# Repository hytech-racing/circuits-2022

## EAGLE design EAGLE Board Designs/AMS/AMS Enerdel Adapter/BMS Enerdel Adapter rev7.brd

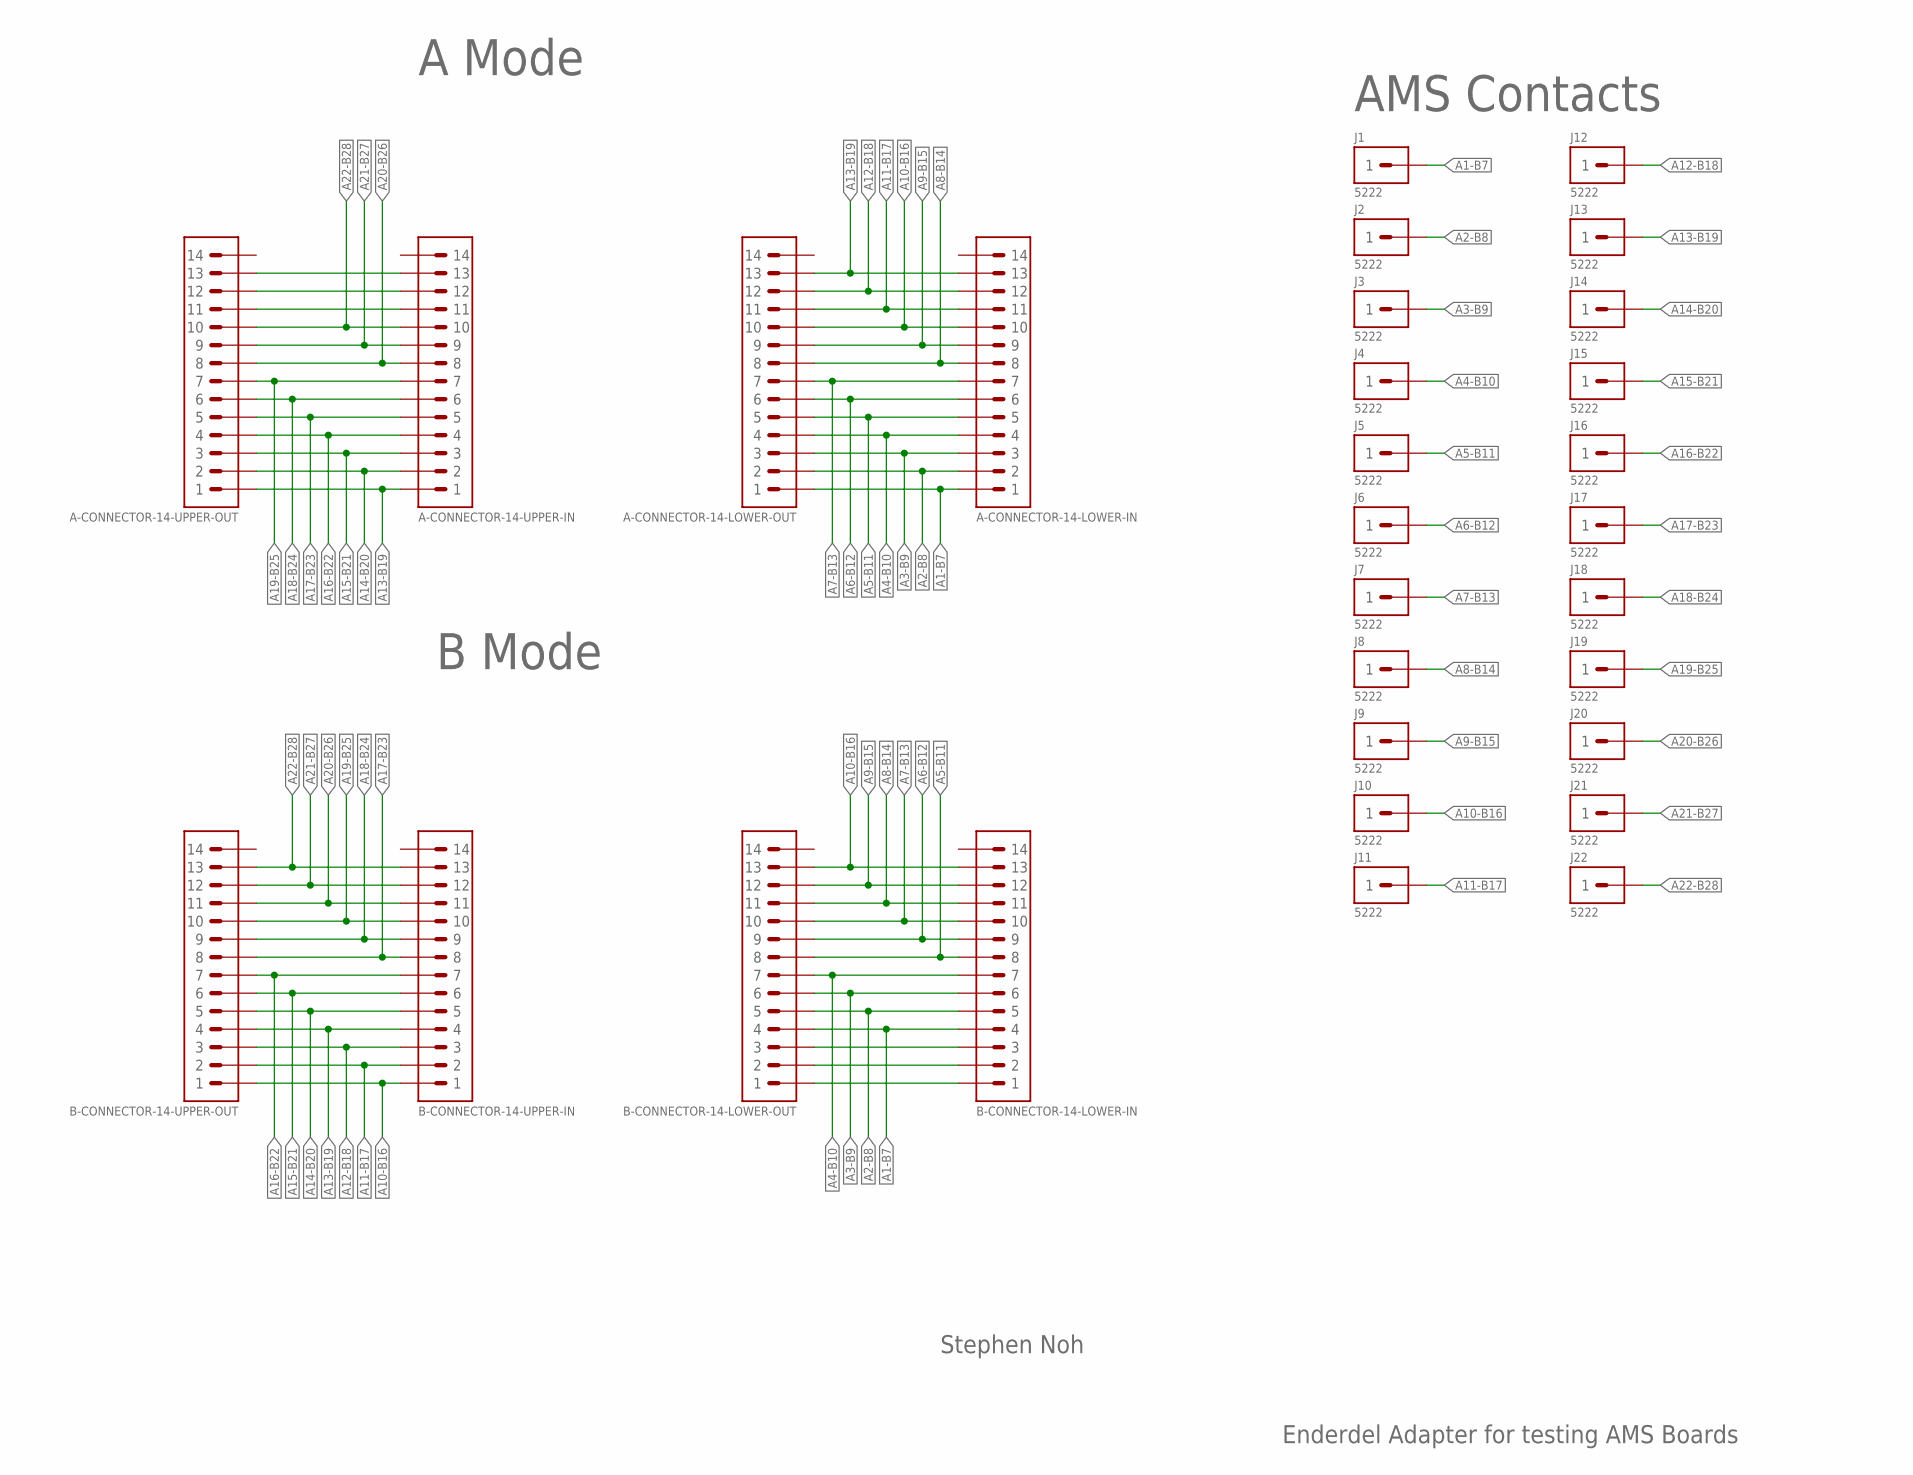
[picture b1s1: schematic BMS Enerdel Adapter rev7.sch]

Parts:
A-CONNECTOR-14-LOWER-IN, A-CONNECTOR-14-LOWER-OUT: CONNECTOR-14_MINIFIT_; MOLEX_MINIFIT_PTH_14
A-CONNECTOR-14-UPPER-IN, A-CONNECTOR-14-UPPER-OUT: CONNECTOR-14_NANOFIT_; MOLEX_NANOFIT_PTH_14
B-CONNECTOR-14-LOWER-IN, B-CONNECTOR-14-LOWER-OUT: CONNECTOR-14_MINIFIT_; MOLEX_MINIFIT_PTH_14
B-CONNECTOR-14-UPPER-IN, B-CONNECTOR-14-UPPER-OUT: CONNECTOR-14_NANOFIT_; MOLEX_NANOFIT_PTH_14
J1, J2, J3, J4, J5, J6, J7, J8, J9, J10, J11, J12, J13, J14, J15, J16, J17, J18, J19, J20, J21, J22: CONNECTOR-1_5222_; 5222

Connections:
A1-B7: A-CONNECTOR-14-LOWER-IN.1, A-CONNECTOR-14-LOWER-OUT.1, B-CONNECTOR-14-LOWER-IN.4, B-CONNECTOR-14-LOWER-OUT.4, J1.1
A2-B8: A-CONNECTOR-14-LOWER-IN.2, A-CONNECTOR-14-LOWER-OUT.2, B-CONNECTOR-14-LOWER-IN.5, B-CONNECTOR-14-LOWER-OUT.5, J2.1
A3-B9: A-CONNECTOR-14-LOWER-IN.3, A-CONNECTOR-14-LOWER-OUT.3, B-CONNECTOR-14-LOWER-IN.6, B-CONNECTOR-14-LOWER-OUT.6, J3.1
A4-B10: A-CONNECTOR-14-LOWER-IN.4, A-CONNECTOR-14-LOWER-OUT.4, B-CONNECTOR-14-LOWER-IN.7, B-CONNECTOR-14-LOWER-OUT.7, J4.1
A5-B11: A-CONNECTOR-14-LOWER-IN.5, A-CONNECTOR-14-LOWER-OUT.5, B-CONNECTOR-14-LOWER-IN.8, B-CONNECTOR-14-LOWER-OUT.8, J5.1
A6-B12: A-CONNECTOR-14-LOWER-IN.6, A-CONNECTOR-14-LOWER-OUT.6, B-CONNECTOR-14-LOWER-IN.9, B-CONNECTOR-14-LOWER-OUT.9, J6.1
A7-B13: A-CONNECTOR-14-LOWER-IN.7, A-CONNECTOR-14-LOWER-OUT.7, B-CONNECTOR-14-LOWER-IN.10, B-CONNECTOR-14-LOWER-OUT.10, J7.1
A8-B14: A-CONNECTOR-14-LOWER-IN.8, A-CONNECTOR-14-LOWER-OUT.8, B-CONNECTOR-14-LOWER-IN.11, B-CONNECTOR-14-LOWER-OUT.11, J8.1
A9-B15: A-CONNECTOR-14-LOWER-IN.9, A-CONNECTOR-14-LOWER-OUT.9, B-CONNECTOR-14-LOWER-IN.12, B-CONNECTOR-14-LOWER-OUT.12, J9.1
A10-B16: A-CONNECTOR-14-LOWER-IN.10, A-CONNECTOR-14-LOWER-OUT.10, B-CONNECTOR-14-LOWER-IN.13, B-CONNECTOR-14-LOWER-OUT.13, B-CONNECTOR-14-UPPER-IN.1, B-CONNECTOR-14-UPPER-OUT.1, J10.1
A11-B17: A-CONNECTOR-14-LOWER-IN.11, A-CONNECTOR-14-LOWER-OUT.11, B-CONNECTOR-14-UPPER-IN.2, B-CONNECTOR-14-UPPER-OUT.2, J11.1
A12-B18: A-CONNECTOR-14-LOWER-IN.12, A-CONNECTOR-14-LOWER-OUT.12, B-CONNECTOR-14-UPPER-IN.3, B-CONNECTOR-14-UPPER-OUT.3, J12.1
A13-B19: A-CONNECTOR-14-LOWER-IN.13, A-CONNECTOR-14-LOWER-OUT.13, A-CONNECTOR-14-UPPER-IN.1, A-CONNECTOR-14-UPPER-OUT.1, B-CONNECTOR-14-UPPER-IN.4, B-CONNECTOR-14-UPPER-OUT.4, J13.1
A14-B20: A-CONNECTOR-14-UPPER-IN.2, A-CONNECTOR-14-UPPER-OUT.2, B-CONNECTOR-14-UPPER-IN.5, B-CONNECTOR-14-UPPER-OUT.5, J14.1
A15-B21: A-CONNECTOR-14-UPPER-IN.3, A-CONNECTOR-14-UPPER-OUT.3, B-CONNECTOR-14-UPPER-IN.6, B-CONNECTOR-14-UPPER-OUT.6, J15.1
A16-B22: A-CONNECTOR-14-UPPER-IN.4, A-CONNECTOR-14-UPPER-OUT.4, B-CONNECTOR-14-UPPER-IN.7, B-CONNECTOR-14-UPPER-OUT.7, J16.1
A17-B23: A-CONNECTOR-14-UPPER-IN.5, A-CONNECTOR-14-UPPER-OUT.5, B-CONNECTOR-14-UPPER-IN.8, B-CONNECTOR-14-UPPER-OUT.8, J17.1
A18-B24: A-CONNECTOR-14-UPPER-IN.6, A-CONNECTOR-14-UPPER-OUT.6, B-CONNECTOR-14-UPPER-IN.9, B-CONNECTOR-14-UPPER-OUT.9, J18.1
A19-B25: A-CONNECTOR-14-UPPER-IN.7, A-CONNECTOR-14-UPPER-OUT.7, B-CONNECTOR-14-UPPER-IN.10, B-CONNECTOR-14-UPPER-OUT.10, J19.1
A20-B26: A-CONNECTOR-14-UPPER-IN.8, A-CONNECTOR-14-UPPER-OUT.8, B-CONNECTOR-14-UPPER-IN.11, B-CONNECTOR-14-UPPER-OUT.11, J20.1
A21-B27: A-CONNECTOR-14-UPPER-IN.9, A-CONNECTOR-14-UPPER-OUT.9, B-CONNECTOR-14-UPPER-IN.12, B-CONNECTOR-14-UPPER-OUT.12, J21.1
A22-B28: A-CONNECTOR-14-UPPER-IN.10, A-CONNECTOR-14-UPPER-OUT.10, B-CONNECTOR-14-UPPER-IN.13, B-CONNECTOR-14-UPPER-OUT.13, J22.1
B-PASS1: B-CONNECTOR-14-LOWER-IN.3, B-CONNECTOR-14-LOWER-OUT.3
B-PASS2: B-CONNECTOR-14-LOWER-IN.2, B-CONNECTOR-14-LOWER-OUT.2
B-PASS3: B-CONNECTOR-14-LOWER-IN.1, B-CONNECTOR-14-LOWER-OUT.1
unnamed: A-CONNECTOR-14-UPPER-IN.11, A-CONNECTOR-14-UPPER-OUT.11
unnamed: A-CONNECTOR-14-UPPER-IN.12, A-CONNECTOR-14-UPPER-OUT.12
unnamed: A-CONNECTOR-14-UPPER-IN.13, A-CONNECTOR-14-UPPER-OUT.13

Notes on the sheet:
Stephen Noh
AMS Contacts
A Mode
Enderdel Adapter for testing AMS Boards
B Mode

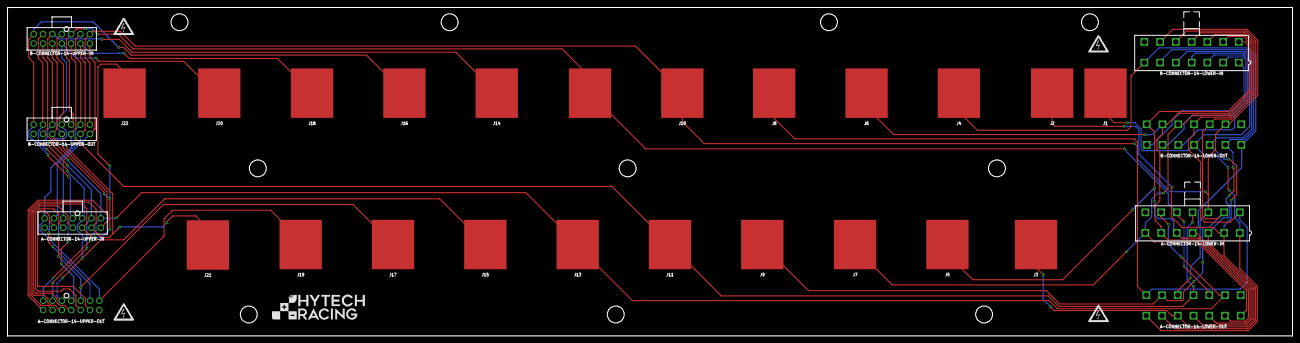
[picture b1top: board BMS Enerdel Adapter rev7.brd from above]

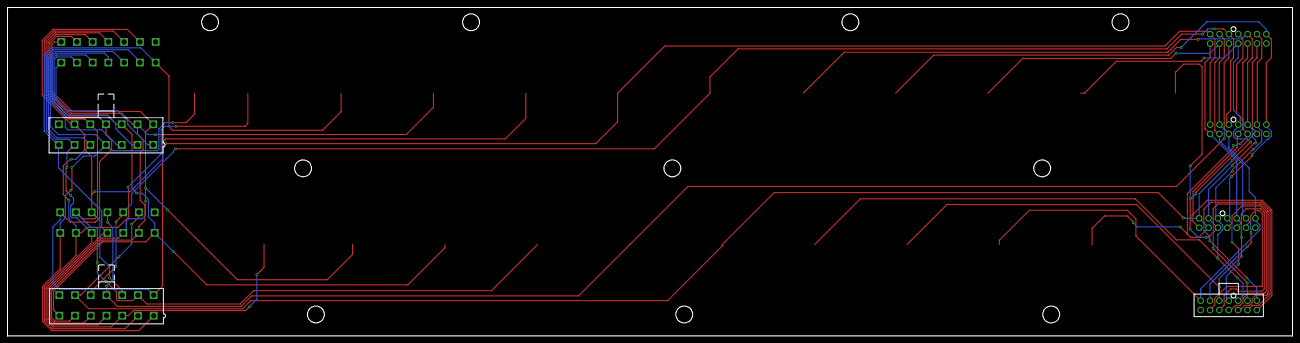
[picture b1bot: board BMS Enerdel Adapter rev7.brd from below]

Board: 2 copper layers, 342.9 x 87.6 mm, 35 parts (3 on the bottom side), 28 nets.

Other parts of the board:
U$1, U$3, U$4, U$5: HV_0.50"
U$2: LOGO_HYTECH_1.0"

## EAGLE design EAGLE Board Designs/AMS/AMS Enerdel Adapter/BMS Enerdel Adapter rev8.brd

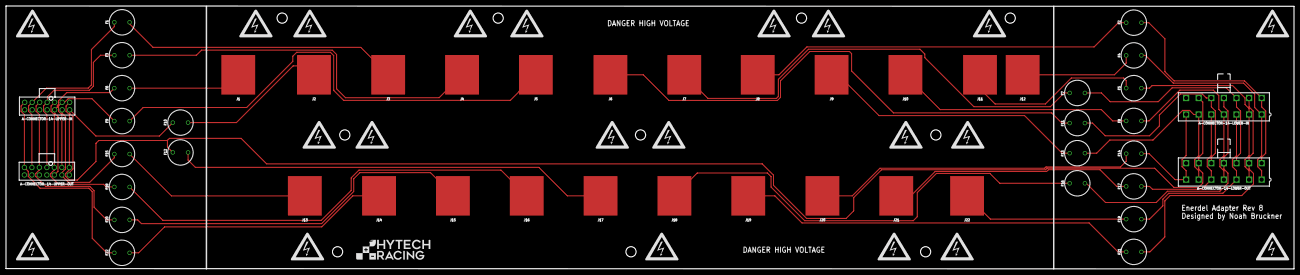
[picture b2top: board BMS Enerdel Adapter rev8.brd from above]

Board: 2 copper layers, 429.8 x 87.7 mm, 80 parts (0 on the bottom side), 44 nets.

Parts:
A-CONNECTOR-14-LOWER-IN, A-CONNECTOR-14-LOWER-OUT: CONNECTOR-14_MINIFIT_; MOLEX_MINIFIT_PTH_14
A-CONNECTOR-14-UPPER-IN, A-CONNECTOR-14-UPPER-OUT: CONNECTOR-14_NANOFIT_; MOLEX_NANOFIT_PTH_14
F1, F2, F3, F4, F5, F6, F7, F8, F9, F10, F11, F12, F13, F14, F15, F16, F17, F18, F19, F20, F21, F22: FUSE_MST_250_.8; MST_250
J1, J2, J3, J4, J5, J6, J7, J8, J9, J10, J11, J12, J13, J14, J15, J16, J17, J18, J19, J20, J21, J22: CONNECTOR-1_5222_; 5222
U$1, U$2, U$3, U$4, U$20, U$21, U$22, U$29, U$30, U$31: MOUNTING_M3
U$5, U$6, U$7, U$8, U$9, U$10, U$11, U$12, U$13, U$14, U$15, U$16, U$17, U$18, U$19, U$23, U$24, U$25, U$26, U$27, U$28: HV_LARGE
U$32: LOGO_HYTECH_1.0"

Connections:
A1-B7: A-CONNECTOR-14-LOWER-IN.1, A-CONNECTOR-14-LOWER-OUT.1, F4.2
A2-B8: A-CONNECTOR-14-LOWER-IN.2, A-CONNECTOR-14-LOWER-OUT.2, F5.2
A3-B9: A-CONNECTOR-14-LOWER-IN.3, A-CONNECTOR-14-LOWER-OUT.3, F19.2
A4-B10: A-CONNECTOR-14-LOWER-IN.4, A-CONNECTOR-14-LOWER-OUT.4, F8.2
A5-B11: A-CONNECTOR-14-LOWER-IN.5, A-CONNECTOR-14-LOWER-OUT.5, F17.2
A6-B12: A-CONNECTOR-14-LOWER-IN.6, A-CONNECTOR-14-LOWER-OUT.6, F13.2
A7-B13: A-CONNECTOR-14-LOWER-IN.7, A-CONNECTOR-14-LOWER-OUT.7, F14.2
A8-B14: A-CONNECTOR-14-LOWER-IN.8, A-CONNECTOR-14-LOWER-OUT.8, F2.2
A9-B15: A-CONNECTOR-14-LOWER-IN.9, A-CONNECTOR-14-LOWER-OUT.9, F21.2
A10-B16: A-CONNECTOR-14-LOWER-IN.10, A-CONNECTOR-14-LOWER-OUT.10, F7.2
A11-B17: A-CONNECTOR-14-LOWER-IN.11, A-CONNECTOR-14-LOWER-OUT.11, F16.2
A12-B18: A-CONNECTOR-14-LOWER-IN.12, A-CONNECTOR-14-LOWER-OUT.12, F11.2
A13-B19: A-CONNECTOR-14-LOWER-IN.13, A-CONNECTOR-14-LOWER-OUT.13, A-CONNECTOR-14-UPPER-IN.1, A-CONNECTOR-14-UPPER-OUT.1, F12.2
A14-B20: A-CONNECTOR-14-UPPER-IN.2, A-CONNECTOR-14-UPPER-OUT.2, F9.2
A15-B21: A-CONNECTOR-14-UPPER-IN.3, A-CONNECTOR-14-UPPER-OUT.3, F18.2
A16-B22: A-CONNECTOR-14-UPPER-IN.4, A-CONNECTOR-14-UPPER-OUT.4, F3.2
A17-B23: A-CONNECTOR-14-UPPER-IN.5, A-CONNECTOR-14-UPPER-OUT.5, F20.2
A18-B24: A-CONNECTOR-14-UPPER-IN.6, A-CONNECTOR-14-UPPER-OUT.6, F1.2
A19-B25: A-CONNECTOR-14-UPPER-IN.7, A-CONNECTOR-14-UPPER-OUT.7, F22.2
A20-B26: A-CONNECTOR-14-UPPER-IN.8, A-CONNECTOR-14-UPPER-OUT.8, F10.2
A21-B27: A-CONNECTOR-14-UPPER-IN.9, A-CONNECTOR-14-UPPER-OUT.9, F15.2
A22-B28: A-CONNECTOR-14-UPPER-IN.10, A-CONNECTOR-14-UPPER-OUT.10, F6.2
unnamed: F4.1, J12.1
unnamed: F5.1, J11.1
unnamed: F19.1, J22.1
unnamed: F8.1, J10.1
unnamed: F17.1, J21.1
unnamed: F13.1, J9.1
unnamed: F14.1, J20.1
unnamed: F2.1, J8.1
unnamed: F21.1, J19.1
unnamed: F7.1, J7.1
unnamed: F16.1, J18.1
unnamed: F6.1, J1.1
unnamed: F15.1, J13.1
unnamed: F10.1, J2.1
unnamed: F22.1, J14.1
unnamed: F1.1, J3.1
unnamed: F20.1, J15.1
unnamed: F3.1, J4.1
unnamed: F18.1, J16.1
unnamed: F9.1, J5.1
unnamed: F11.1, J6.1
unnamed: F12.1, J17.1

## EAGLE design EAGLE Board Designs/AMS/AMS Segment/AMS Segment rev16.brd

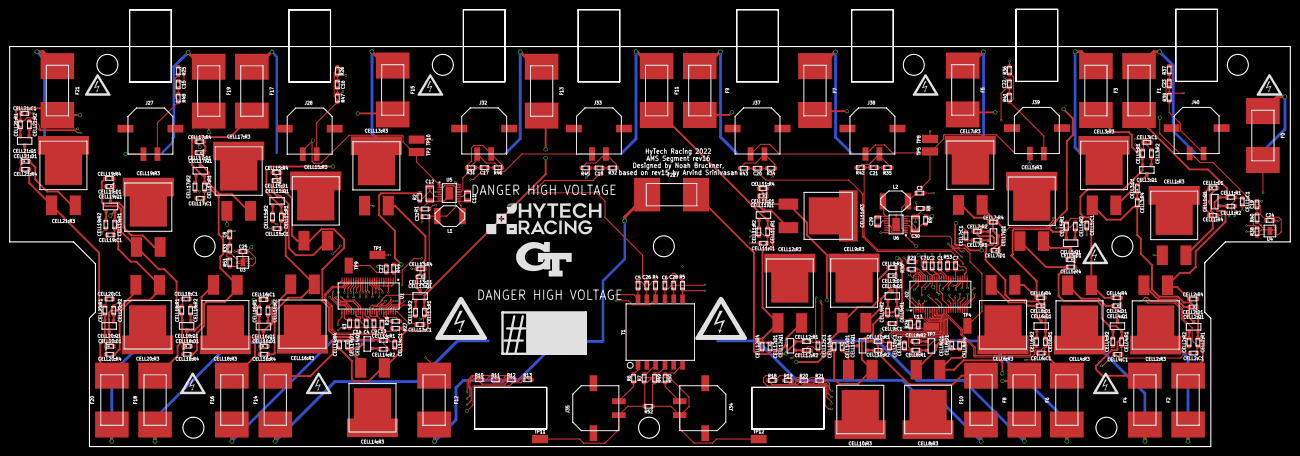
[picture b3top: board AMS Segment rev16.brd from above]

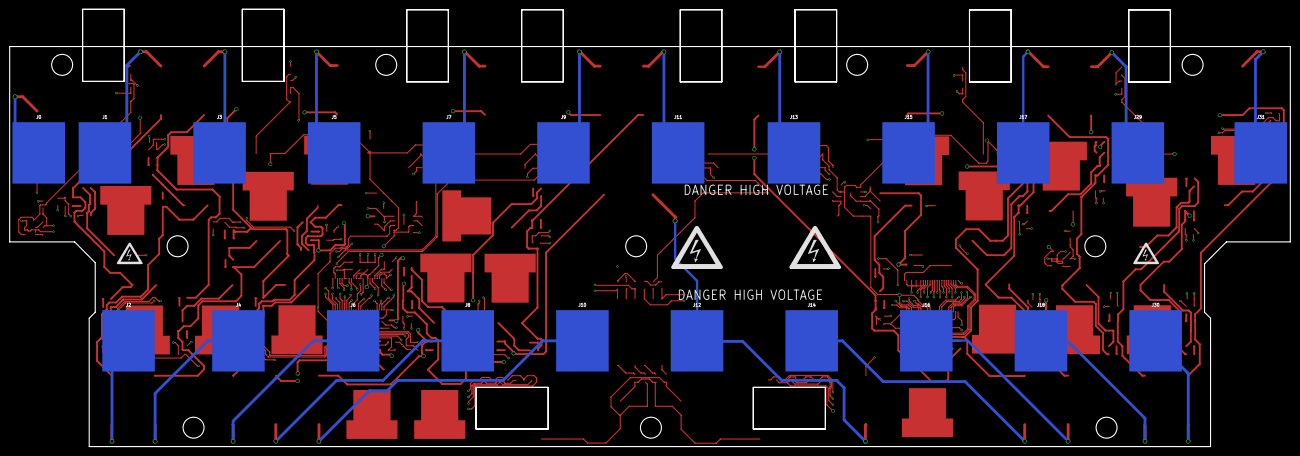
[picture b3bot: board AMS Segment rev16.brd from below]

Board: 4 copper layers, 275.2 x 94.0 mm, 329 parts (26 on the bottom side), 214 nets.

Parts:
C1, C2, C4, C9, C31, C32: CAPACITOR_0603_10V_1UF; 0603-CAP
C3, C10: CAPACITOR_0603_10V_22UF; 0603-CAP
C5, C6: CAPACITOR_0603_10V_15PF; 0603-CAP
C7, C14, C15, C16, C17, C18, C20, C21, C22, C23: CAPACITOR_0603_100V_10NF; 0603-CAP
C8, C19: CAPACITOR_0603_10V_3.3NF; 0603-CAP
C11, C29: CAPACITOR_0805_100V_0.22UF; 0805-CAP
C12, C30: CAPACITOR_1206_100V_2.2UF; 1206-CAP
C13, C27: CAPACITOR_0603_100V_0.1UF; 0603-CAP
C24, C25: CAPACITOR_0603_10V_0.1UF; 0603-CAP
C26, C28: CAPACITOR_0603_10V_10NF; 0603-CAP
CELL1:C1, CELL2:C1, CELL3:C1, CELL4:C1, CELL5:C1, CELL6:C1, CELL7:C1, CELL8:C1, CELL9:C1, CELL10:C1, CELL11:C1, CELL12:C1, CELL13:C1, CELL14:C1, CELL15:C1, CELL16:C1, CELL17:C1, CELL18:C1, CELL19:C1, CELL20:C1, CELL21:C1: CAPACITOR_0603_100V_10NF; 0603-CAP
CELL1:D1, CELL2:D1, CELL3:D1, CELL4:D1, CELL5:D1, CELL6:D1, CELL7:D1, CELL8:D1, CELL9:D1, CELL10:D1, CELL11:D1, CELL12:D1, CELL13:D1, CELL14:D1, CELL15:D1, CELL16:D1, CELL17:D1, CELL18:D1, CELL19:D1, CELL20:D1, CELL21:D1: LED_0603_RED; 0603-LED
CELL1:Q1, CELL2:Q1, CELL3:Q1, CELL4:Q1, CELL5:Q1, CELL6:Q1, CELL7:Q1, CELL8:Q1, CELL9:Q1, CELL10:Q1, CELL11:Q1, CELL12:Q1, CELL13:Q1, CELL14:Q1, CELL15:Q1, CELL16:Q1, CELL17:Q1, CELL18:Q1, CELL19:Q1, CELL20:Q1, CELL21:Q1: TRANSISTOR_P_MOS_SOT23_SI2369DS-T1-GE3; SOT-23
CELL1:R1, CELL2:R1, CELL3:R1, CELL4:R1, CELL5:R1, CELL6:R1, CELL7:R1, CELL8:R1, CELL9:R1, CELL10:R1, CELL11:R1, CELL12:R1, CELL13:R1, CELL14:R1, CELL15:R1, CELL16:R1, CELL17:R1, CELL18:R1, CELL19:R1, CELL20:R1, CELL21:R1: RESISTOR_0603_100; 0603-RES
CELL1:R2, CELL1:R4, CELL2:R2, CELL2:R4, CELL3:R2, CELL3:R4, CELL4:R2, CELL4:R4, CELL5:R2, CELL5:R4, CELL6:R2, CELL6:R4, CELL7:R2, CELL7:R4, CELL8:R2, CELL8:R4, CELL9:R2, CELL9:R4, CELL10:R2, CELL10:R4, CELL11:R2, CELL11:R4, CELL12:R2, CELL12:R4, CELL13:R2, CELL13:R4, CELL14:R2, CELL14:R4, CELL15:R2, CELL15:R4, CELL16:R2, CELL16:R4, CELL17:R2, CELL17:R4, CELL18:R2, CELL18:R4, CELL19:R2, CELL19:R4, CELL20:R2, CELL20:R4, CELL21:R2, CELL21:R4: RESISTOR_0603_1K; 0603-RES
CELL1:R3, CELL2:R3, CELL3:R3, CELL4:R3, CELL5:R3, CELL6:R3, CELL7:R3, CELL8:R3, CELL9:R3, CELL10:R3, CELL11:R3, CELL12:R3, CELL13:R3, CELL14:R3, CELL15:R3, CELL16:R3, CELL17:R3, CELL18:R3, CELL19:R3, CELL20:R3, CELL21:R3: RESISTOR_PWR263_7.5; PWR263
F0, F1, F2, F3, F4, F5, F6, F7, F8, F9, F10, F11, F12, F13, F14, F15, F16, F17, F18, F19, F20, F21, F22: FUSE_0885_1.6; 0885
J0, J1, J2, J3, J4, J5, J6, J7, J8, J9, J10, J11, J12, J13, J14, J15, J16, J17, J18, J29, J30, J31: CONNECTOR-1_5222_; 5222
J27, J28, J32, J33, J34, J35, J37, J38, J39, J40: CONNECTOR-2_MICROFIT_SMD_RIGHTANGLE_02_SINGLE_BLA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; MOLEX_MICROFIT_SMD_RIGHTANGLE_02_SINGLE
L1, L2: INDUCTOR_74451133_33UH; 74451133
R1, R8: RESISTOR_0603_374K; 0603-RES
R2, R9: RESISTOR_0603_470; 0603-RES
R3, R24, R33, R38, R39, R41, R42, R43, R44, R45, R46, R47, R48, R53: RESISTOR_0603_100; 0603-RES
R4, R5: RESISTOR_0603_402; 0603-RES
R6, R7, R49, R50: RESISTOR_0603_22; 0603-RES
R10, R11, R12, R13, R18, R19, R20, R21, R40, R51, R52: RESISTOR_0603_DNP; 0603-RES
R25, R26, R31, R32, R34, R35, R36, R37: RESISTOR_0603_2.74K; 0603-RES
R27, R28, R29, R30: RESISTOR_0603_1K; 0603-RES
T1: TRANSFORMER_HM2112ZNLT; HM2112ZNLT
TP1, TP2, TP4, TP5, TP7, TP8, TP9, TP10, TP11, TP12: TEST_POINT; MICRO_MINIATURE
U1, U2: LTC6811-2; SSOP-48
U3, U4: SHT31-ARP-B; DFN-8
U5, U6: LT3990-5; MSOP-16(MSE)
U$1, U$4, U$5, U$6, U$11, U$12, U$13, U$14, U$15, U$16: MOUNTING_M4
U$2: LOGO_HYTECH_1.0"
U$3: LOGO_GT_0.50"
U$7: NUMBER
U$8, U$9, U$10, U$17, U$18, U$19, U$20, U$22, U$28, U$29: HV_0.50"
U$21, U$25: DANGER_HIGH_VOLTAGE
U$23, U$24, U$26, U$27: HV_1.00"

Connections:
C0L: C7.1, R53.2, U2.26
C0U: C14.1, R3.2, U1.26
C1L: CELL1:C1.1, CELL1:R1.2, U2.24
C1U: CELL13:C1.1, CELL13:R1.2, U1.24
C2L: CELL2:C1.1, CELL2:R1.2, U2.22
C2U: CELL14:C1.1, CELL14:R1.2, U1.22
C3L: CELL3:C1.1, CELL3:R1.2, U2.20
C3U: CELL15:C1.1, CELL15:R1.2, U1.20
C4L: CELL4:C1.1, CELL4:R1.2, U2.18
C4U: CELL16:C1.1, CELL16:R1.2, U1.18
C5L: CELL5:C1.1, CELL5:R1.2, U2.16
C5U: CELL17:C1.1, CELL17:R1.2, U1.16
C6L: CELL6:C1.1, CELL6:R1.2, U2.14
C6U: CELL18:C1.1, CELL18:R1.2, U1.14
C7L: CELL7:C1.1, CELL7:R1.2, U2.12
C7U: CELL19:C1.1, CELL19:R1.2, U1.12
C8L: CELL8:C1.1, CELL8:R1.2, U2.10
C8U: CELL20:C1.1, CELL20:R1.2, U1.10
C9L: CELL9:C1.1, CELL9:R1.2, U2.8
C9U: CELL21:C1.1, CELL21:R1.2, U1.2, U1.4, U1.6, U1.8
C10L: CELL10:C1.1, CELL10:R1.2, U2.6
C11L: CELL11:C1.1, CELL11:R1.2, U2.4
C12L: CELL12:C1.1, CELL12:R1.2, U2.2
CC0: F0.1, J0.1
CC1: F1.1, J1.1
CC2: F2.1, J2.1
CC3: F3.1, J3.1
CC4: F4.1, J4.1
CC5: F5.1, J5.1
CC6: F6.1, J6.1
CC7: F7.1, J7.1
CC8: F8.1, J8.1
CC9: F9.1, J9.1
CC10: F10.1, J10.1
CC11: F11.1, J11.1
CC12: F12.1, F22.1, J12.1
CC13: F13.1, J13.1
CC14: F14.1, J14.1
CC15: F15.1, J15.1
CC16: F16.1, J16.1
CC17: F17.1, J17.1
CC18: F18.1, J18.1
CC19: F19.1, J29.1
CC20: F20.1, J30.1
CC21: F21.1, J31.1
CELL1:N$5: CELL1:Q1.1, CELL1:R2.1
CELL1:N$6: CELL1:D1.2, CELL1:Q1.3, CELL1:R3.2
CELL1:N$7: CELL1:D1.1, CELL1:R4.2
CELL2:N$5: CELL2:Q1.1, CELL2:R2.1
CELL2:N$6: CELL2:D1.2, CELL2:Q1.3, CELL2:R3.2
CELL2:N$7: CELL2:D1.1, CELL2:R4.2
CELL3:N$5: CELL3:Q1.1, CELL3:R2.1
CELL3:N$6: CELL3:D1.2, CELL3:Q1.3, CELL3:R3.2
CELL3:N$7: CELL3:D1.1, CELL3:R4.2
CELL4:N$5: CELL4:Q1.1, CELL4:R2.1
CELL4:N$6: CELL4:D1.2, CELL4:Q1.3, CELL4:R3.2
CELL4:N$7: CELL4:D1.1, CELL4:R4.2
CELL5:N$5: CELL5:Q1.1, CELL5:R2.1
CELL5:N$6: CELL5:D1.2, CELL5:Q1.3, CELL5:R3.2
CELL5:N$7: CELL5:D1.1, CELL5:R4.2
CELL6:N$5: CELL6:Q1.1, CELL6:R2.1
CELL6:N$6: CELL6:D1.2, CELL6:Q1.3, CELL6:R3.2
CELL6:N$7: CELL6:D1.1, CELL6:R4.2
CELL7:N$5: CELL7:Q1.1, CELL7:R2.1
CELL7:N$6: CELL7:D1.2, CELL7:Q1.3, CELL7:R3.2
CELL7:N$7: CELL7:D1.1, CELL7:R4.2
CELL8:N$5: CELL8:Q1.1, CELL8:R2.1
CELL8:N$6: CELL8:D1.2, CELL8:Q1.3, CELL8:R3.2
CELL8:N$7: CELL8:D1.1, CELL8:R4.2
CELL9:N$5: CELL9:Q1.1, CELL9:R2.1
CELL9:N$6: CELL9:D1.2, CELL9:Q1.3, CELL9:R3.2
CELL9:N$7: CELL9:D1.1, CELL9:R4.2
CELL10:N$5: CELL10:Q1.1, CELL10:R2.1
CELL10:N$6: CELL10:D1.2, CELL10:Q1.3, CELL10:R3.2
CELL10:N$7: CELL10:D1.1, CELL10:R4.2
CELL11:N$5: CELL11:Q1.1, CELL11:R2.1
CELL11:N$6: CELL11:D1.2, CELL11:Q1.3, CELL11:R3.2
CELL11:N$7: CELL11:D1.1, CELL11:R4.2
CELL12:N$5: CELL12:Q1.1, CELL12:R2.1
CELL12:N$6: CELL12:D1.2, CELL12:Q1.3, CELL12:R3.2
CELL12:N$7: CELL12:D1.1, CELL12:R4.2
CELL13:N$5: CELL13:Q1.1, CELL13:R2.1
CELL13:N$6: CELL13:D1.2, CELL13:Q1.3, CELL13:R3.2
CELL13:N$7: CELL13:D1.1, CELL13:R4.2
CELL14:N$5: CELL14:Q1.1, CELL14:R2.1
CELL14:N$6: CELL14:D1.2, CELL14:Q1.3, CELL14:R3.2
CELL14:N$7: CELL14:D1.1, CELL14:R4.2
CELL15:N$5: CELL15:Q1.1, CELL15:R2.1
CELL15:N$6: CELL15:D1.2, CELL15:Q1.3, CELL15:R3.2
CELL15:N$7: CELL15:D1.1, CELL15:R4.2
CELL16:N$5: CELL16:Q1.1, CELL16:R2.1
CELL16:N$6: CELL16:D1.2, CELL16:Q1.3, CELL16:R3.2
CELL16:N$7: CELL16:D1.1, CELL16:R4.2
CELL17:N$5: CELL17:Q1.1, CELL17:R2.1
CELL17:N$6: CELL17:D1.2, CELL17:Q1.3, CELL17:R3.2
CELL17:N$7: CELL17:D1.1, CELL17:R4.2
CELL18:N$5: CELL18:Q1.1, CELL18:R2.1
CELL18:N$6: CELL18:D1.2, CELL18:Q1.3, CELL18:R3.2
CELL18:N$7: CELL18:D1.1, CELL18:R4.2
CELL19:N$5: CELL19:Q1.1, CELL19:R2.1
CELL19:N$6: CELL19:D1.2, CELL19:Q1.3, CELL19:R3.2
CELL19:N$7: CELL19:D1.1, CELL19:R4.2
CELL20:N$5: CELL20:Q1.1, CELL20:R2.1
CELL20:N$6: CELL20:D1.2, CELL20:Q1.3, CELL20:R3.2
CELL20:N$7: CELL20:D1.1, CELL20:R4.2
CELL21:N$5: CELL21:Q1.1, CELL21:R2.1
CELL21:N$6: CELL21:D1.2, CELL21:Q1.3, CELL21:R3.2
CELL21:N$7: CELL21:D1.1, CELL21:R4.2
DRVL: TP4.1, U2.38, U6.4
DRVU: TP1.1, U1.38, U5.4
GPIO1L: C20.1, R43.2, U2.27
GPIO1U: C15.1, R48.2, U1.27
GPIO2L: C21.1, R42.2, U2.28
GPIO2U: C16.1, R47.2, U1.28
GPIO3L: C22.1, R41.2, U2.29
GPIO3U: C17.1, R46.2, U1.29
GPIO4L: C23.1, R39.2, U2.32
GPIO4U: C18.1, R45.2, U1.32
GPIO5L: C19.1, R38.1, R40.1, U2.33
GPIO5U: C8.1, R33.1, R51.1, U1.33
IM: J34.2, J35.2, R6.1, R49.1, R52.1, TP12.1
IML: C6.2, T1.9, U2.41
IMU: C5.2, T1.12, U1.41
IP: J34.1, J35.1, R7.1, R50.1, R52.2, TP11.1
IPL: R5.2, T1.7, U2.42
IPU: R4.2, T1.10, U1.42
unnamed: R1.2, U5.16
unnamed: C11.2, L1.1, U5.9
unnamed: C11.1, U5.11
unnamed: R8.2, U6.16
unnamed: C29.2, L2.1, U6.9
unnamed: C29.1, U6.11
unnamed: R33.2, U3.1
unnamed: C26.2, T1.11
unnamed: R6.2, T1.1
unnamed: R10.2, R11.2, U1.46
unnamed: R7.2, T1.3
unnamed: C28.2, T1.8
unnamed: R51.2, U3.4
unnamed: R49.2, T1.4
unnamed: R50.2, T1.6
unnamed: R12.2, R13.2, U1.47
unnamed: R27.2, R28.2, U1.43
unnamed: R18.2, R19.2, U2.46
unnamed: R20.2, R21.2, U2.47
unnamed: R28.1, U1.44
unnamed: J27.2, R25.1, R48.1
unnamed: R29.2, R30.1, U2.43
unnamed: R30.2, U2.44
unnamed: J28.2, R26.1, R47.1
unnamed: J32.2, R31.1, R46.1
unnamed: J33.2, R32.1, R45.1
unnamed: R40.2, U4.1
unnamed: R38.2, U4.4
unnamed: J37.2, R34.1, R43.1
unnamed: J38.2, R35.1, R42.1
unnamed: J39.2, R36.1, R41.1
unnamed: J40.2, R37.1, R39.1
unnamed: C5.1, R4.1
unnamed: C6.1, R5.1
S1L: CELL1:R2.2, U2.25
S1U: CELL13:R2.2, U1.25
S2L: CELL2:R2.2, U2.23
S2U: CELL14:R2.2, U1.23
S3L: CELL3:R2.2, U2.21
S3U: CELL15:R2.2, U1.21
S4L: CELL4:R2.2, U2.19
S4U: CELL16:R2.2, U1.19
S5L: CELL5:R2.2, U2.17
S5U: CELL17:R2.2, U1.17
S6L: CELL6:R2.2, U2.15
S6U: CELL18:R2.2, U1.15
S7L: CELL7:R2.2, U2.13
S7U: CELL19:R2.2, U1.13
S8L: CELL8:R2.2, U2.11
S8U: CELL20:R2.2, U1.11
S9L: CELL9:R2.2, U2.9
S9U: CELL21:R2.2, U1.9
S10L: CELL10:R2.2, U2.7
S11L: CELL11:R2.2, U2.5
S12L: CELL12:R2.2, U2.3
SENSE1: CELL1:Q1.2, CELL1:R1.1, CELL2:R3.1, CELL2:R4.1, F1.2
SENSE2: CELL2:Q1.2, CELL2:R1.1, CELL3:R3.1, CELL3:R4.1, F2.2
SENSE3: CELL3:Q1.2, CELL3:R1.1, CELL4:R3.1, CELL4:R4.1, F3.2
SENSE4: CELL4:Q1.2, CELL4:R1.1, CELL5:R3.1, CELL5:R4.1, F4.2
SENSE5: CELL5:Q1.2, CELL5:R1.1, CELL6:R3.1, CELL6:R4.1, F5.2
SENSE6: CELL6:Q1.2, CELL6:R1.1, CELL7:R3.1, CELL7:R4.1, F6.2
SENSE7: CELL7:Q1.2, CELL7:R1.1, CELL8:R3.1, CELL8:R4.1, F7.2
SENSE8: CELL8:Q1.2, CELL8:R1.1, CELL9:R3.1, CELL9:R4.1, F8.2
SENSE9: CELL9:Q1.2, CELL9:R1.1, CELL10:R3.1, CELL10:R4.1, F9.2
SENSE10: CELL10:Q1.2, CELL10:R1.1, CELL11:R3.1, CELL11:R4.1, F10.2
SENSE11: CELL11:Q1.2, CELL11:R1.1, CELL12:R3.1, CELL12:R4.1, F11.2
SENSE12: CELL12:Q1.2, CELL12:R1.1, F22.2, R9.1, R24.2
SENSE13: CELL13:Q1.2, CELL13:R1.1, CELL14:R3.1, CELL14:R4.1, F13.2
SENSE14: CELL14:Q1.2, CELL14:R1.1, CELL15:R3.1, CELL15:R4.1, F14.2
SENSE15: CELL15:Q1.2, CELL15:R1.1, CELL16:R3.1, CELL16:R4.1, F15.2
SENSE16: CELL16:Q1.2, CELL16:R1.1, CELL17:R3.1, CELL17:R4.1, F16.2
SENSE17: CELL17:Q1.2, CELL17:R1.1, CELL18:R3.1, CELL18:R4.1, F17.2
SENSE18: CELL18:Q1.2, CELL18:R1.1, CELL19:R3.1, CELL19:R4.1, F18.2
SENSE19: CELL19:Q1.2, CELL19:R1.1, CELL20:R3.1, CELL20:R4.1, F19.2
SENSE20: CELL20:Q1.2, CELL20:R1.1, CELL21:R3.1, CELL21:R4.1, F20.2
SENSE21: CELL21:Q1.2, CELL21:R1.1, F21.2, R2.1, R44.1
V+L: C13.1, R24.1, TP7.1, U2.1
V+U: C27.1, R44.2, TP9.1, U1.1
V-L: C1.2, C2.2, C3.2, C7.2, C13.2, C19.2, C20.2, C21.2, C22.2, C23.2, C24.2, C28.1, C30.2, C31.2, CELL1:C1.2, CELL1:R3.1, CELL1:R4.1, CELL2:C1.2, CELL3:C1.2, CELL4:C1.2, CELL5:C1.2, CELL6:C1.2, CELL7:C1.2, CELL8:C1.2, CELL9:C1.2, CELL10:C1.2, CELL11:C1.2, CELL12:C1.2, F0.2, R8.1, R18.1, R20.1, R29.1, R34.2, R35.2, R36.2, R37.2, R53.1, TP8.1, U2.30, U2.31, U2.45, U2.48, U4.2, U4.3, U4.7, U4.8, U4.PAD, U6.8, U6.17
V-U: C4.2, C8.2, C9.2, C10.2, C12.2, C14.2, C15.2, C16.2, C17.2, C18.2, C25.2, C26.1, C27.2, C32.2, CELL13:C1.2, CELL13:R3.1, CELL13:R4.1, CELL14:C1.2, CELL15:C1.2, CELL16:C1.2, CELL17:C1.2, CELL18:C1.2, CELL19:C1.2, CELL20:C1.2, CELL21:C1.2, F12.2, R1.1, R3.1, R10.1, R12.1, R25.2, R26.2, R27.1, R31.2, R32.2, TP10.1, U1.30, U1.31, U1.48, U3.2, U3.3, U3.7, U3.8, U3.PAD, U5.8, U5.17
VINL: C30.1, R9.2, U6.6
VINU: C12.1, R2.2, U5.6
VREF1L: C2.1, U2.35
VREF1U: C9.1, U1.35
VREF2L: C1.1, U2.34
VREF2U: C4.1, U1.34
VREGL: C3.1, C24.1, C31.1, J37.1, J38.1, J39.1, J40.1, L2.2, R19.1, R21.1, TP5.1, U2.36, U2.37, U2.40, U4.5, U6.1, U6.2, U6.13
VREGU: C10.1, C25.1, C32.1, J27.1, J28.1, J32.1, J33.1, L1.2, R11.1, R13.1, TP2.1, U1.36, U1.37, U1.40, U1.45, U3.5, U5.1, U5.2, U5.13

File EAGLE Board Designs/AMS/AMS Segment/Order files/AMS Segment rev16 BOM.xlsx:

Qty | Value | Device | Package | Parts | Description | CAPACITANCE | COLOR | CURRENT | CURRENT_RATED | CURRENT_SATURATION | DCR | DKPN | INDUCTANCE | MANUFACTURER | MODEL | MOPN | MPN | POWER | RESISTANCE | TOLERANCE | VOLTAGE | VOLTAGE_CONTINUOUS | VOLTAGE_MAX | Column1
2 | CAPACITOR_0603_100V_0.1UF | CAPACITOR_0603_100V_0.1UF | 0603-CAP | C13, C27 | Capacitor, Non-Polarized | 0.1ÂµF |  |  |  |  |  | 311-1523-1-ND |  | Yageo |  | 603-CC603KRX7R0BB104 | CC0603KRX7R0BB104 |  |  | 0.1 | 100V
31 | CAPACITOR_0603_100V_10NF | CAPACITOR_0603_100V_10NF | 0603-CAP | C7, C14, C15, C16, C17, C18, C20, C21, C22, C23, CELL1:C1, CELL2:C1, CELL3:C1, 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 | Capacitor, Non-Polarized | 10nF |  |  |  |  |  | 311-1788-1-ND |  | Yageo |  | 603-CC603KRX7R0BB103 | CC0603KRX7R0BB103 |  |  | 0.1 | 100V
2 | CAPACITOR_0603_10V_0.1UF | CAPACITOR_0603_10V_0.1UF | 0603-CAP | C24, C25 | Capacitor, Non-Polarized | 0.1ÂµF |  |  |  |  |  | 720-1688-1-ND |  | Vishay Vitramon |  | 77-VJ0603Y104JXQPBC | VJ0603Y104JXQPW1BC |  |  | 0.05 | 10V
2 | CAPACITOR_0603_10V_10NF | CAPACITOR_0603_10V_10NF | 0603-CAP | C26, C28 | Capacitor, Non-Polarized | 10nF |  |  |  |  |  | 311-4054-1-ND |  | Yageo |  | 603-CC603KRX7R6BB103 | CC0603KRX7R6BB103 |  |  | 0.1 | 10V
2 | CAPACITOR_0603_10V_15PF | CAPACITOR_0603_10V_15PF | 0603-CAP | C5, C6 | Capacitor, Non-Polarized | 15pF |  |  |  |  |  | 720-VJ0603A150FXQPW1BCCT-ND |  | Vishay Vitramon |  | 77-VJ0603A150FXQPBC | VJ0603A150FXQPW1BC |  |  | 0.01 | 10V
6 | CAPACITOR_0603_10V_1UF | CAPACITOR_0603_10V_1UF | 0603-CAP | C1, C2, C4, C9, C31, C32 | Capacitor, Non-Polarized | 1ÂµF |  |  |  |  |  | 311-1796-1-ND |  | Yageo |  | 603-CC603KRX7R6BB105 | CC0603KRX7R6BB105 |  |  | 0.1 | 10V
2 | CAPACITOR_0603_10V_22UF | CAPACITOR_0603_10V_22UF | 0603-CAP | C3, C10 | Capacitor, Non-Polarized | 22ÂµF |  |  |  |  |  | 490-10476-1-ND |  | Murata Electronics |  | 81-GRM188R61A226ME5D | GRM188R61A226ME15D |  |  | 0.2 | 10V
2 | CAPACITOR_0603_10V_3.3NF | CAPACITOR_0603_10V_3.3NF | 0603-CAP | C8, C19 | Capacitor, Non-Polarized | 3.3nF |  |  |  |  |  | 732-7759-1-ND |  | WÃ¼rth Elektronik |  | 710-885012006016 | 885012006016 |  |  | 0.05 | 10V
2 | CAPACITOR_0805_100V_0.22UF | CAPACITOR_0805_100V_0.22UF | 0805-CAP | C11, C29 | Capacitor, Non-Polarized | 0.22ÂµF |  |  |  |  |  | 399-8049-1-ND |  | KEMET |  | 80-C0805C224K1R | C0805C224K1RACTU |  |  | 0.1 | 100V
2 | CAPACITOR_1206_100V_2.2UF | CAPACITOR_1206_100V_2.2UF | 1206-CAP | C12, C30 | Capacitor, Non-Polarized | 2.2ÂµF |  |  |  |  |  | 478-12144-1-ND |  | AVX Corporation |  | 581-12061C225K4T2A | 12061C225K4T2A |  |  | 0.1 | 100V
22 | CONNECTOR-1_5222_ | CONNECTOR-1_5222_ | 5222 | J0, J1, J2, J3, J4, J5, J6, J7, J8, J9, J10, J11, J12, J13, J14, J15, J16, J17,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 | 1 Pin Connector |  |  |  |  |  |  | 36-5222-ND |  | Keystone Electronics | SPRING | 534-5222 | 5222
10 | CONNECTOR-2_MICROFIT_SMD_RIGHTANGLE_02_SINGLE_BLACK | CONNECTOR-2_MICROFIT_SMD_RIGHTANGLE_02_SINGLE_BLACK | MOLEX_MICROFIT_SMD_RIGHTANGLE_02_SINGLE | J27, J28, J32, J33, J34, J35, J37, J38, J39, J40 | 2 Pin Connector |  |  |  |  |  |  | 436500214 |  | Molex |  | 538-43650-0214 | 436500214
23 | FUSE_0885_1.6 | FUSE_0885_1.6 | 0885 | F0, F1, F2, F3, F4, F5, F6, F7, F8, F9, F10, F11, F12, F13, F14, F15, F16, F17,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 | Fuse |  |  | 1.6A |  |  |  | F10987CT-ND |  | Littelfuse Inc. |  | 576-088501.6DR | 088501.6DR |  |  |  | 500V
2 | INDUCTOR_74451133_33UH | INDUCTOR_74451133_33UH | 74451133 | L1, L2 | Inductor |  |  |  | 0.6A | 0.15A | 0.19Î© | 732-1410-1-ND | 33ÂµH | WÃ¼rth Elektronik |  | 710-74451133 | 74451133 |  |  | 0.2
21 | LED_0603_RED | LED_0603_RED | 0603-LED | CELL1:D1, CELL2:D1, CELL3:D1, CELL4:D1, CELL5:D1, CELL6:D1, CELL7:D1, CELL8:D1,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 | LED |  | Red |  |  |  |  | 754-1786-1-ND |  | Kingbright |  | 604-APT1608SECKJ3PRV | APT1608SECK/J3-PRV
2 | LT3990-5 | LT3990-5 | MSOP-16(MSE) | U5, U6 | LT3990-5 DC-DC Converter |  |  |  |  |  |  | LT3990EMSE-5#PBF-ND |  | Analog Devices Inc. |  | 584-LT3990EMSE-5#PBF | LT3990EMSE-5#PBF
2 | LTC6811-2 | LTC6811-2 | SSOP-48 | U1, U2 | LTC6811-2 12 Cell Stackable Battery Monitor |  |  |  |  |  |  | LTC6811IG-2#3ZZPBF-ND |  | Analog Devices Inc. |  | 584-6811IG-2#3ZZPB | LTC6811IG-2#3ZZPBF
35 | RESISTOR_0603_100 | RESISTOR_0603_100 | 0603-RES | CELL1:R1, CELL2:R1, CELL3:R1, CELL4:R1, CELL5:R1, CELL6:R1, CELL7:R1, CELL8:R1,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 | Resistor |  |  |  |  |  |  | 311-100HRCT-ND |  | Yageo |  | 603-RC0603FR-07100RL | RC0603FR-07100RL | 0.1W | 100 | 0.01 |  | 3.16V | 75V
46 | RESISTOR_0603_1K | RESISTOR_0603_1K | 0603-RES | CELL1:R2, CELL1:R4, CELL2:R2, CELL2:R4, CELL3:R2, CELL3:R4, CELL4:R2, CELL4:R4,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 | Resistor |  |  |  |  |  |  | 311-1.00KHRCT-ND |  | Yageo |  | 603-RC0603FR-071KL | RC0603FR-071KL | 0.1W | 1k | 0.01 |  | 10.00V | 75V
8 | RESISTOR_0603_2.74K | RESISTOR_0603_2.74K | 0603-RES | R25, R26, R31, R32, R34, R35, R36, R37 | Resistor |  |  |  |  |  |  | P20020CT-ND |  | Panasonic Electronic Components |  | 667-ERJ-PB3B2741V | ERJ-PB3B2741V | 0.2W | 2.74k | 1E-3 |  | 23.41V | 150V
4 | RESISTOR_0603_22 | RESISTOR_0603_22 | 0603-RES | R6, R7, R49, R50 | Resistor |  |  |  |  |  |  | 311-22.0HRCT-ND |  | Yageo |  | 603-RC0603FR-0722RL | RC0603FR-0722RL | 0.1W | 22 | 0.01 |  | 1.48V | 75V
2 | RESISTOR_0603_374K | RESISTOR_0603_374K | 0603-RES | R1, R8 | Resistor |  |  |  |  |  |  | 311-374KHRCT-ND |  | Yageo |  | 603-RC0603FR-07374KL | RC0603FR-07374KL | 0.1W | 374k | 0.01 |  | 75V | 75V
2 | RESISTOR_0603_402 | RESISTOR_0603_402 | 0603-RES | R4, R5 | Resistor |  |  |  |  |  |  | 311-402HRCT-ND |  | Yageo |  | 603-RC0603FR-07402RL | RC0603FR-07402RL | 0.1W | 402 | 0.01 |  | 6.34V | 75V
2 | RESISTOR_0603_470 | RESISTOR_0603_470 | 0603-RES | R2, R9 | Resistor |  |  |  |  |  |  | P470BYCT-ND |  | Panasonic Electronic Components |  | 667-ERJ-PA3F4700V | ERJ-PA3F4700V | 0.25W | 470 | 0.01 |  | 10.84V | 150V
11 | RESISTOR_0603_DNP | RESISTOR_0603_DNP | 0603-RES | R10, R11, R12, R13, R18, R19, R20, R21, R40, R51, R52 | Resistor |  |  |  |  |  |  |  |  |  |  |  |  |  | DNP
21 | RESISTOR_PWR263_7.5 | RESISTOR_PWR263_7.5 | PWR263 | CELL1:R3, CELL2:R3, CELL3:R3, CELL4:R3, CELL5:R3, CELL6:R3, CELL7:R3, CELL8:R3,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 | Resistor |  |  |  |  |  |  | PWR263S-35-7R50J-ND |  | Bourns Inc. |  | 652-PWR263S357R50J | PWR263S-35-7R50J | 3.5W | 7.5 | 0.05 |  | 5.123V | 5.123V
2 | SHT31-ARP-B | SHT31-ARP-B | DFN-8 | U3, U4 | Humidity and Temperature Sensor |  |  |  |  |  |  | 1649-1012-1-ND |  | Sensirion AG |  | 403-SHT31-ARP-B | SHT31-ARP-B
10 | TEST_POINT | TEST_POINT | MICRO_MINIATURE | TP1, TP2, TP4, TP5, TP7, TP8, TP9, TP10, TP11, TP12 | Test Point |  |  |  |  |  |  | 36-5015CT-ND |  | Keystone Electronics |  | 534-5015 | 5015
1 | TRANSFORMER_HM2112ZNLT | TRANSFORMER_HM2112ZNLT | HM2112ZNLT | T1 | 2 Channel SMT Transformer |  |  |  |  |  |  | 1840-1036-1-ND |  | Pulse Electronics |  | 673-HM2112ZNLT | HM2112ZNLT
21 | TRANSISTOR_P_MOS_SOT23_SI2369DS-T1-GE3 | TRANSISTOR_P_MOS_SOT23_SI2369DS-T1-GE3 | SOT-23 | CELL1:Q1, CELL2:Q1, CELL3:Q1, CELL4:Q1, CELL5:Q1, CELL6:Q1, CELL7:Q1, CELL8:Q1,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 | MOSFET P Channel |  |  |  |  |  |  | SI2369DS-T1-GE3CT-ND |  | Vishay Siliconix |  | 78-SI2369DS-T1-GE3 | SI2369DS-T1-GE3
